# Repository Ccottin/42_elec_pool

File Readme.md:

# ˚. ✧̣̇.⋆˳.✦ .˚    Bill Of Materials    ˚. ✦.˳⋆.✧̣̇. ˚

| Reference     | Qty | Value         | DNP | Exclude from BOM | Exclude from Board | Footprint                              | Datasheet | Unit Price | Ext Price |
|--------------|-----|---------------|-----|-------------------|---------------------|-----------------------------------------|-----------|------------|-----------|
| C1,C3,C4     | 3   | 100nF         |     |                   |                     | 42_footprint:Capacitor_100nf           |           | 0.0024     | 0.0072    |
| C2           | 1   | 1uF           |     |                   |                     | 42_footprint:Capacitor_1uf             |           | 0.0049     | 0.0049    |
| C5,C6        | 2   | 12pF          |     |                   |                     | 42_footprint:Capacitor_12pf            |           | 0.0048     | 0.0048    |
| D1           | 1   | Green         |     |                   |                     | 42_footprint:Led_Green                 |           | 0.0081     | 0.0081    |
| D2           | 1   | Red           |     |                   |                     | 42_footprint:Led_Red                   |           | 0.0032     | 0.0032    |
| J1,J2        | 2   | ~             |     |                   |                     | 42_footprint:Connector_12_2.54pitch    |           |            |           |
| J3           | 1   | FTDI          |     |                   |                     | 42_footprint:Connector_6_2.54pitch     |           |            |           |
| R1,R3        | 2   | 10K           |     |                   |                     | 42_footprint:Resistance_10k            |           | 0.0011     | 0.0011    |
| R2           | 1   | 330           |     |                   |                     | 42_footprint:Resistance_330            |           | 0.0011     | 0.0011    |
| SW1          | 1   | ~             |     |                   |                     | 42_footprint:Switch                    |           | 0.1189     | 0.1189    |
| U1           | 1   | Atmega328P-A  |     |                   |                     | 42_footprint:Atmega328p-au             |           | 1.6088     | 1.6088    |
| Y1           | 1   | 16MHz         |     |                   |                     | 42_footprint:Crystal Oscillator        |           | 0.0662     | 0.0662    |

# ˚. ✧̣̇.⋆˳.✦ .˚  Pin Layout   ˚. ✦.˳⋆.✧̣̇. ˚

     +----------------------------+
     | [ ]D9               D10[ ] |  
     | [ ]D8     +---+     D11[ ] |  
     | [ ]D7    -| U |-    D12[ ] |   
     | [ ]D6    -| N |-    D13[ ] |   
     | [ ]D5    -| I |-     A0[ ] |   
     | [ ]D4    -| C |-     A1[ ] |   
     | [ ]D3    -| O |-     A2[ ] |
     | [ ]D2    -| R |-     A3[ ] |   
     | [ ]GND   -| N |-     5V[ ] |   
     | [ ]RST    +---+     RST[ ] |   
     | [ ]RXI              GND[ ] |  
     | [ ]TXO              RAW[ ] | 
     |                            | 
     |  GND GND RAW RXI TXO DTR   | 
     |  [ ] [ ] [ ] [ ] [ ] [ ]   |
     \____________________________/

Credits : https://busyducks.com/ascii-art-arduino-pinouts/

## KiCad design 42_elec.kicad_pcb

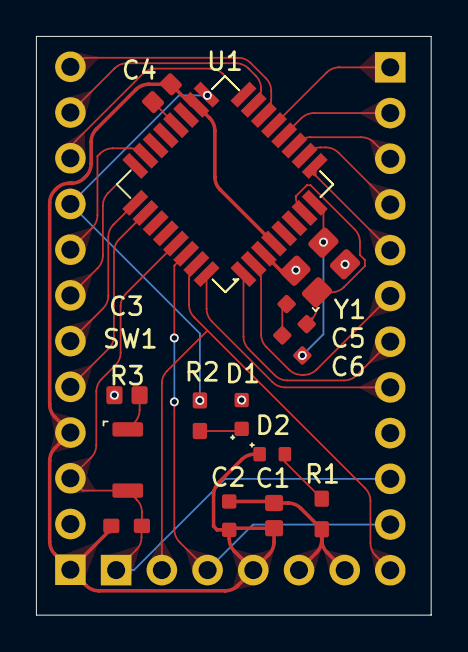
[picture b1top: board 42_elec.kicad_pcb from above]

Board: 2 copper layers, 21.9 x 32.1 mm, 17 parts (0 on the bottom side), 28 nets.

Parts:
C1, C3, C4: 100nF; Capacitor_100nf
C2: 1uF; Capacitor_1uf
C5, C6: 12pF; Capacitor_12pf
D1: Green; Led_Green
D2: Red; Led_Red
J1, J2: Connector_12_2.54pitch
J3: FTDI; Connector_6_2.54pitch
R1, R3: 10K; Resistance_10k
R2: 330; Resistance_330
SW1: Switch
U1: Atmega328P-A; Atmega328p-au
Y1: 16MHz; Crystal Oscillator

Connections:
A0: J2.8, U1.23 (PC0)
A1: J2.7, U1.24 (PC1)
A2: J2.6, U1.25 (PC2)
A3: J2.5, U1.26 (PC3)
D2: J1.8, U1.32 (PD2)
D3: J1.7, U1.1 (PD3)
D4: J1.6, U1.2 (PD4)
D5: J1.5, U1.9 (PD5)
D6: J1.4, U1.10 (PD6)
D7: J1.3, U1.11 (PD7)
D8: J1.2, U1.12 (PB0)
D9: J1.1, U1.13 (PB1)
D10: J2.12, U1.14 (PB2)
DTR: J1.10, J2.3, J3.1, R3.1, SW1.2, U1.29 (RESET/PC6)
GND: C1.2, C2.2, C3.1, D1.1, J1.9, J2.2, J3.5, J3.6, R1.2, U1.3 (GND), Y1.2, Y1.4
MISO: J2.10, U1.16 (PB4)
MOSI: J2.11, U1.15 (PB3)
unnamed: C3.2, SW1.1
unnamed: C5.2, C6.2
unnamed: D1.2, R2.2
unnamed: D2.1, R1.1
unnamed: C4.2, U1.20 (AREF)
unnamed: C5.1, U1.7 (XTAL1/PB6), Y1.1
unnamed: C6.1, U1.8 (XTAL2/PB7), Y1.3
RAW: C1.1, C2.1, C4.1, D2.2, J2.1, J2.4, J3.4, R3.2, U1.4 (VCC), U1.18 (AVCC)
RXI: J1.11, J3.3, U1.30 (PD0)
SCK: J2.9, R2.1, U1.17 (PB4)
TXO: J1.12, J3.2, U1.31 (PD1)

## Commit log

2025-11-25 All is working but it is not cleaned
2025-11-25 Readme & Pdf added, a little cleaned, It should be good
2025-11-25 Cleanse
2025-11-26 More cleanse
